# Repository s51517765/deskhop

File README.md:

# DeskHop - Fast Desktop Switching

## 概要 (Overview)

このプロジェクトは https://github.com/hrvach/deskhop のForkです。

[Original README.md](README_original.md)

以下はオリジナルより引用。

テクノロジーのクレイジーな世界では、競合相手が左利き用ドライバーと自動的に隠れる目覚まし時計だけかもしれないほどニッチな問題を解決しようとする、風変わりな小さなプロジェクトが常に存在することに気づいたことがありますか?

私は毎日のワークフローで 2 台の異なるコンピューターを使用しており、それらの間で 1 つのキーボードとマウスのペアを共有しています。 Amazon で見つけたいくつかの USB スイッチング ボックスを試してみたところ、どれも同様の問題を抱えていることがわかりました。切り替えには時間がかかり、ボタンを探すときのプロセスは非常にぎこちなく、率直に言って、時間が経っても改善されません。

私が欲しかったのは、キーボード ショートカットを使用して出力をすばやく切り替える方法と、マウス ポインタを魔法のようにモニタ間で移動することで同じことを行う機能です。 このプロジェクトを使用すると、コンピュータで異なるオペレーティング システムが実行されている場合でも、両方を行うことができます。

## オリジナルとの差分（Differences from Original）

タクトスイッチ（Board B）にPC Bのマウス速度を切り替える機能を追加

## 動画 (Movie)

https://twitter.com/s51517765/status/1760995792129872011

## 実装イメージ (Pictures)

オリジナルに対して、タクトスイッチを2つ追加している。

## 動作要件 (Requirements)

RaspberryPi Pico / C++

## 部品リスト (Parts List)

|部品|種類|数量|秋月コード|価格|
| ------------- | ------------- |------------- |------------- |------------- |
|基板取付用USBコネクタ|Aタイプ メス|2個|115180|50*2|
|タクトスイッチ|TVBP06-B043CR-B|2個【オプション】|108213|20*2|
|デジタルアイソレーター|ADuM121N1BRZ|1個|113619|320|
|チップ積層セラミックコンデンサー|0.1μF100V C0G 3216|1パック5個入|115180|120|
|Raspberry Pi Pico|-|2個|116132|770*2|
|USB Type B microケーブル|-|2個|-|-|

部品についてはオリジナルの部品リストから、同等のものを秋月電子のラインナップから選定した。USB Type B microケーブルについては一般的なものが使用できるはずである。

## ライセンス (License)
 GNU GENERAL PUBLIC LICENSE Version 3, 29 June 2007

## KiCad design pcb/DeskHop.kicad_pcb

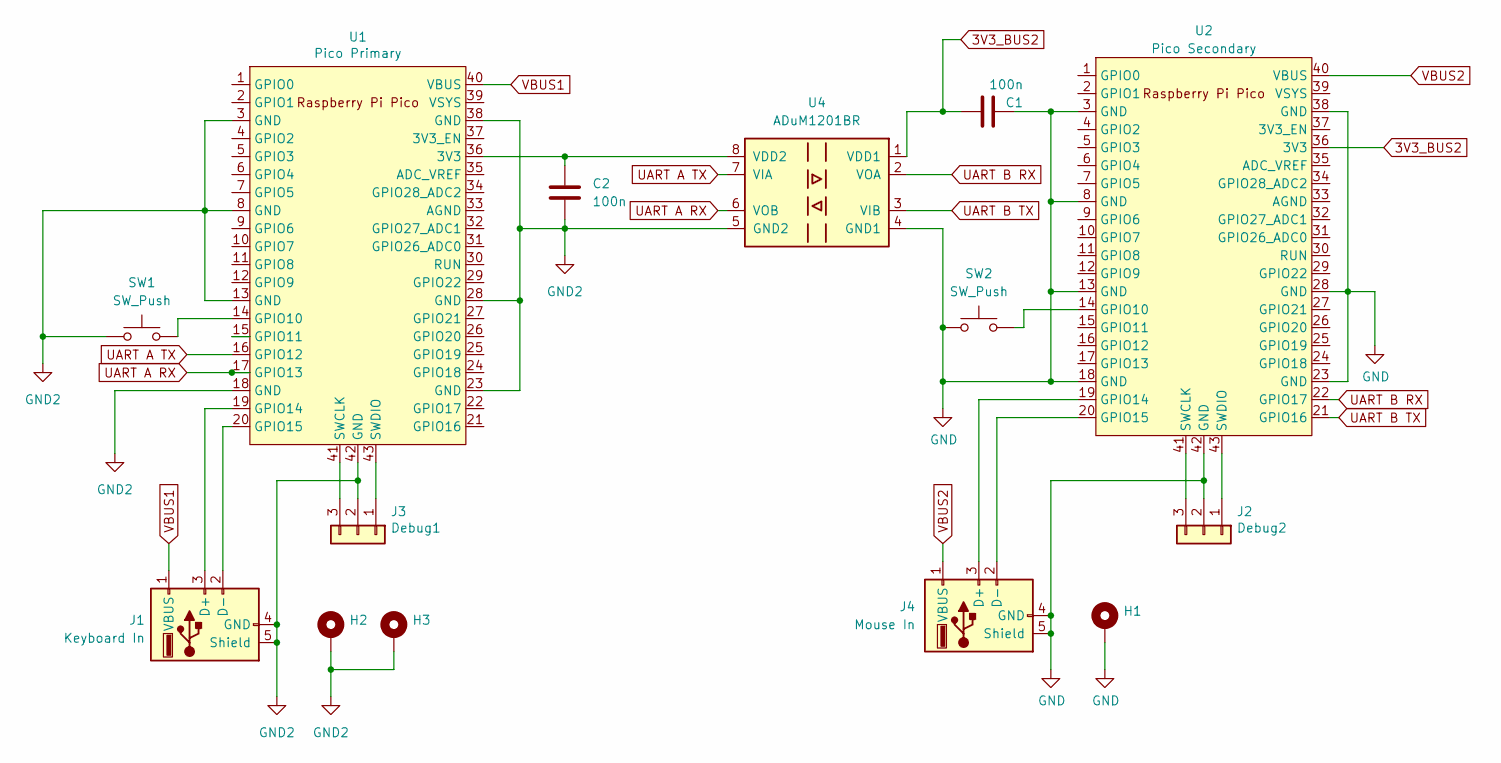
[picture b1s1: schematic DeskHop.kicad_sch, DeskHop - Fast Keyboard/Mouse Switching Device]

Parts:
C1, C2: 100n; C_1206_3216Metric_Pad1.33x1.80mm_HandSolder
H1, H2: MountingHole_Pad; MountingHole_2.7mm_M2.5_Pad_TopBottom
H3: MountingHole_Pad; MountingHole_2.7mm_M2.5_Pad_TopOnly
J1: Keyboard In; USB_A_Molex_67643_Horizontal
J2: Debug2; PinHeader_1x03_P2.54mm_Vertical
J3: Debug1; PinHeader_1x03_P2.54mm_Vertical
J4: Mouse In; USB_A_Molex_67643_Horizontal
SW1, SW2: SW_Push; SW_PUSH_1P1T_6x3.5mm_H5.0_APEM_MJTP1250
U1: Pico Primary; RPi_Pico_SMD_Nohole
U2: Pico Secondary; RPi_Pico_SMD_Nohole
U4: ADuM1201BR; SOIC-8_3.9x4.9mm_P1.27mm

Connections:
3V3_BUS2: C1.1, U2.36 (3V3), U4.1 (VDD1)
GND: C1.2, H1.1, J2.2, J4.4 (GND), J4.5 (Shield), SW2.1, U2.3 (GND), U2.8 (GND), U2.13 (GND), U2.18 (GND), U2.23 (GND), U2.28 (GND), U2.38 (GND), U2.42 (GND), U4.4 (GND1)
GND2: C2.2, H2.1, H3.1, J1.4 (GND), J1.5 (Shield), J3.2, SW1.1, U1.3 (GND), U1.8 (GND), U1.13 (GND), U1.18 (GND), U1.23 (GND), U1.28 (GND), U1.38 (GND), U1.42 (GND), U4.5 (GND2)
unnamed: J1.3 (D+), U1.19 (GPIO14)
unnamed: J1.2 (D-), U1.20 (GPIO15)
unnamed: J2.1, U2.43 (SWDIO)
unnamed: J2.3, U2.41 (SWCLK)
unnamed: J3.1, U1.43 (SWDIO)
unnamed: J3.3, U1.41 (SWCLK)
unnamed: J4.3 (D+), U2.19 (GPIO14)
unnamed: J4.2 (D-), U2.20 (GPIO15)
unnamed: C2.1, U1.36 (3V3), U4.8 (VDD2)
unnamed: SW1.2, U1.14 (GPIO10)
unnamed: SW2.2, U2.14 (GPIO10)
UART A RX: U1.17 (GPIO13), U4.6 (VOB)
UART A TX: U1.16 (GPIO12), U4.7 (VIA)
UART B RX: U2.22 (GPIO17), U4.2 (VOA)
UART B TX: U2.21 (GPIO16), U4.3 (VIB)
VBUS1: J1.1 (VBUS), U1.40 (VBUS)
VBUS2: J4.1 (VBUS), U2.40 (VBUS)

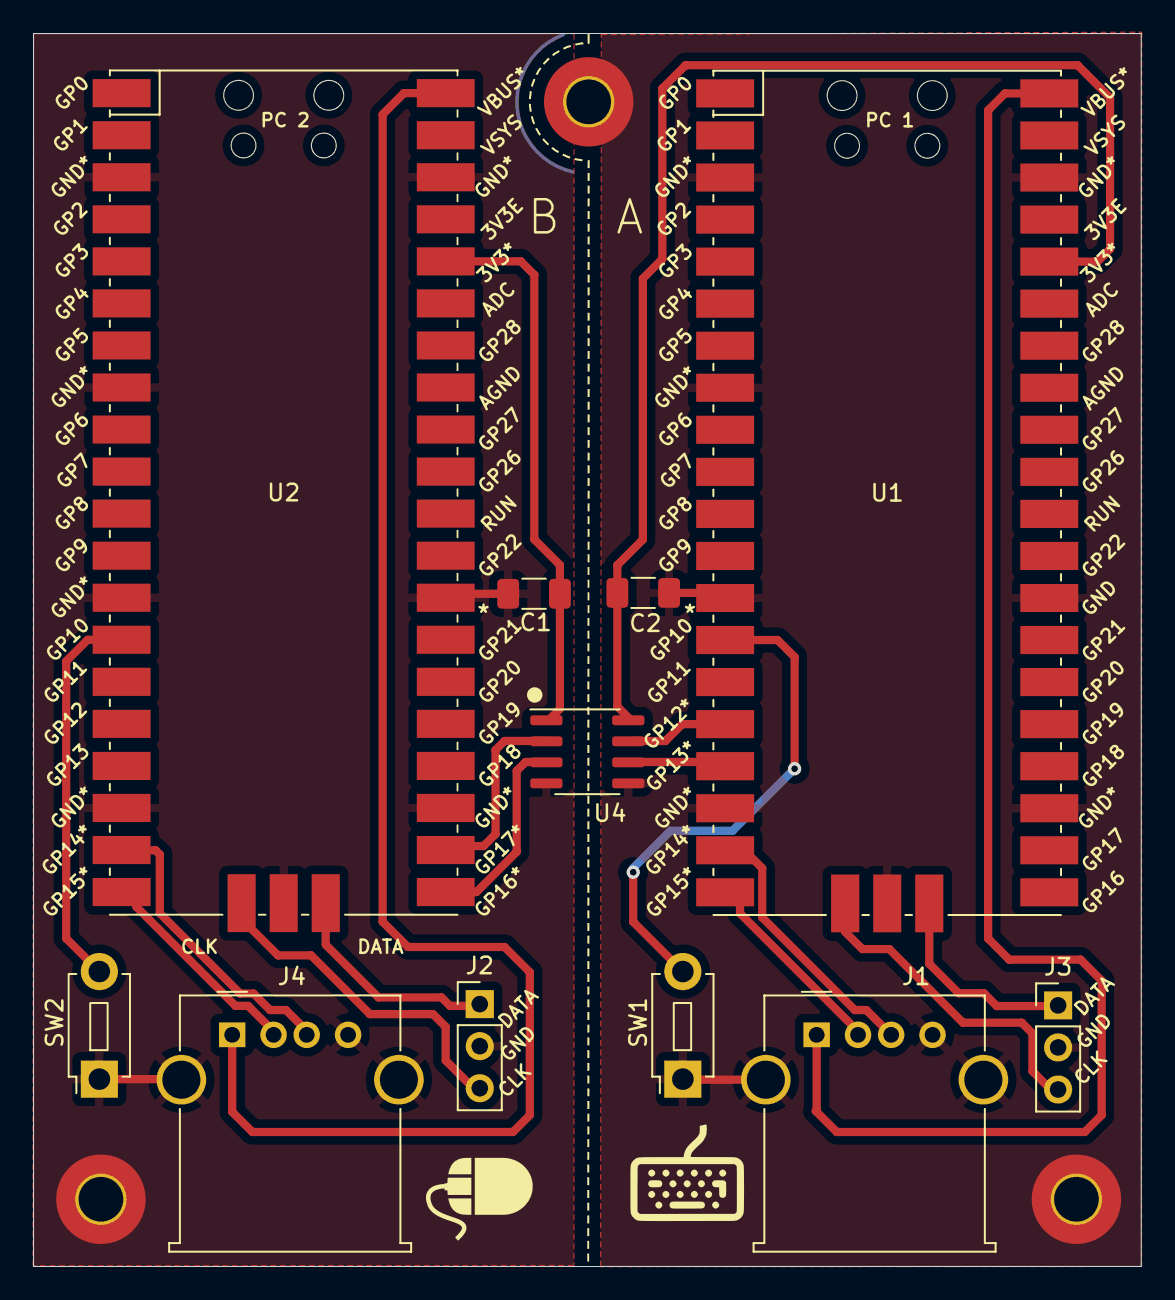
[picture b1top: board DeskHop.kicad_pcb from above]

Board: 2 copper layers, 66.9 x 74.5 mm, 14 parts (0 on the bottom side), 20 nets.

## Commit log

2024-02-23 Add switch to PCB board
2024-02-23 Add schematics.pdf
2024-03-16 Add switch-B function
2024-03-16 誤記訂正
2024-03-17 Refactoring
